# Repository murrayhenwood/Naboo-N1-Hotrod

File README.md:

## Naboo-N1-Hotrod

issue and changes tracking for https://www.thingiverse.com/thing:5220540

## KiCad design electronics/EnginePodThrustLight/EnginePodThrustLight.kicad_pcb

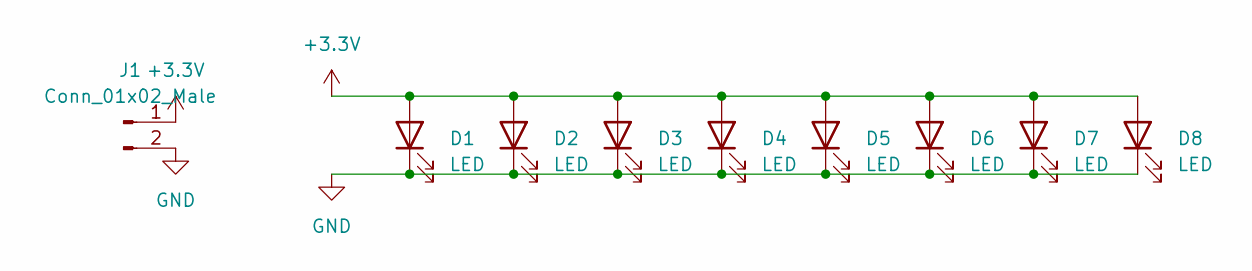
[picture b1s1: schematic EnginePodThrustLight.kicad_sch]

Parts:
D1, D2, D3, D4, D5, D6, D7, D8: LED; D_1206_3216Metric_Pad1.42x1.75mm_HandSolder
J1: Conn_01x02_Male; PinHeader_1x02_P2.54mm_Vertical

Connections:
+3V3: D1.2 (A), D2.2 (A), D3.2 (A), D4.2 (A), D5.2 (A), D6.2 (A), D7.2 (A), D8.2 (A), J1.1
GND: D1.1 (K), D2.1 (K), D3.1 (K), D4.1 (K), D5.1 (K), D6.1 (K), D7.1 (K), D8.1 (K), J1.2

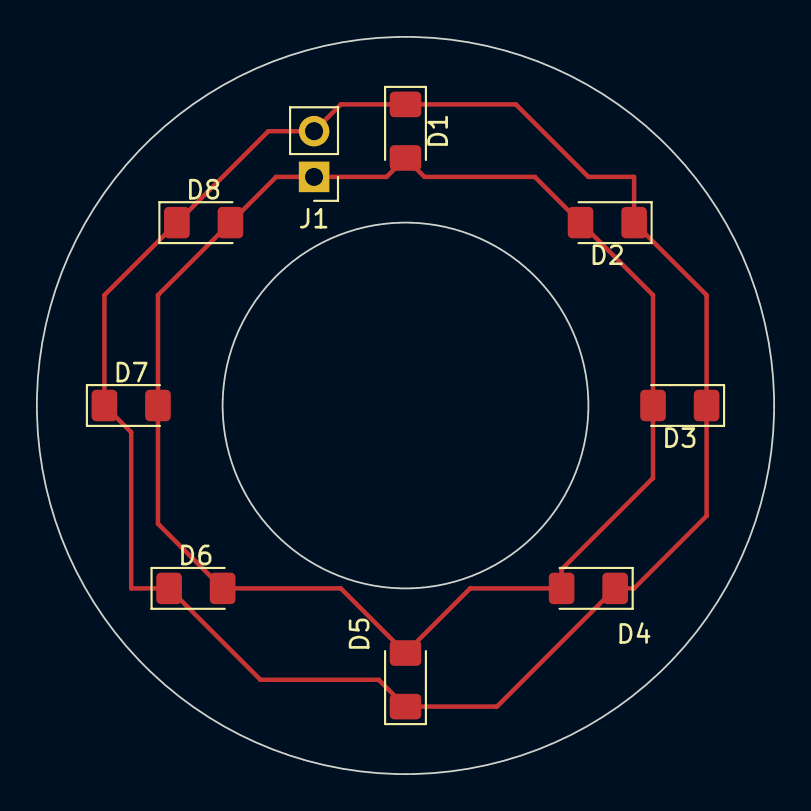
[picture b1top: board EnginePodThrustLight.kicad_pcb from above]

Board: 2 copper layers, 41.0 x 41.0 mm, 9 parts (0 on the bottom side), 2 nets.

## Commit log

2022-01-28 Initial
2022-01-29 v0-1-1
2022-01-29 PCB design
2022-02-02 v0-2-0
